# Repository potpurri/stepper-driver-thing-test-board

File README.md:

# stepper-driver-thing-test-board

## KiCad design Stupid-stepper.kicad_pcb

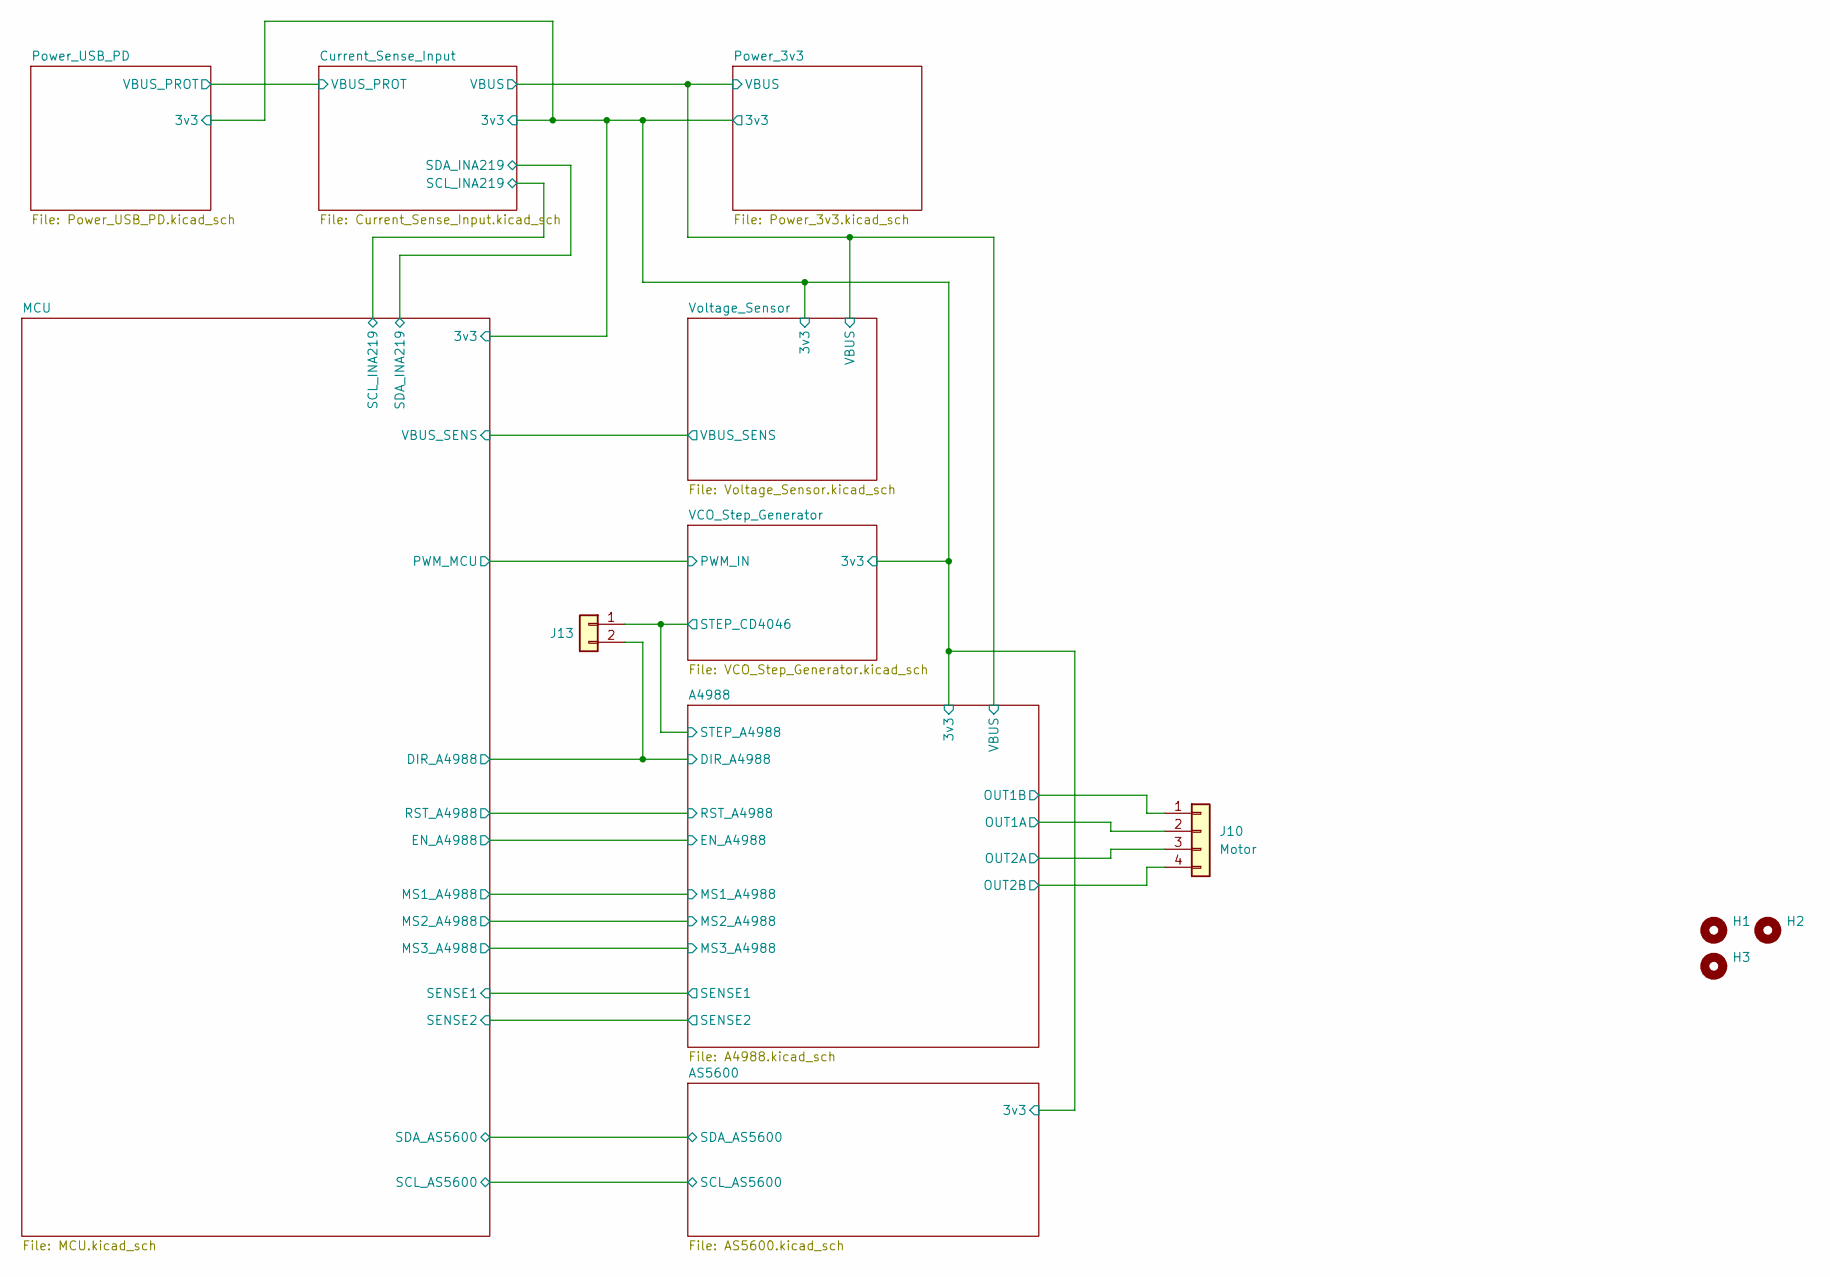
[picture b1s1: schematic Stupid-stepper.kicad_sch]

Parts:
H1, H2, H3: MountingHole; MountingHole_3.2mm_M3_DIN965_Pad_TopBottom
J10: Motor; JST_PH_B4B-PH-K_1x04_P2.00mm_Vertical
J13: Conn_01x02; PinHeader_1x02_P2.54mm_Vertical

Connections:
/A4988/DIR_A4988: J13.2; also elsewhere on the board
/A4988/OUT1A: J10.2; also elsewhere on the board
/A4988/OUT1B: J10.1; also elsewhere on the board
/A4988/OUT2A: J10.3; also elsewhere on the board
/A4988/OUT2B: J10.4; also elsewhere on the board
/A4988/STEP_A4988: J13.1; also elsewhere on the board

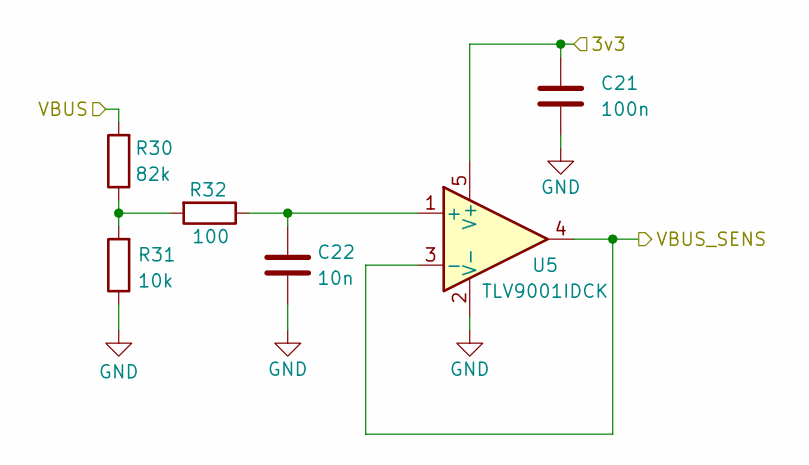
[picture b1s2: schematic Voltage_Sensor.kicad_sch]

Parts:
C21: 100n; C_0603_1608Metric
C22: 10n; C_0603_1608Metric
R30: 82k; R_0603_1608Metric
R31: 10k; R_0603_1608Metric
R32: 100; R_0603_1608Metric
U5: TLV9001IDCK; SOT-353_SC-70-5

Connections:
+3.3V: C21.1, U5.5 (V+); also elsewhere on the board
/MCU/VBUS_SENS: U5.3 (-), U5.4; also elsewhere on the board
GND: C21.2, C22.2, R31.1, U5.2 (V-); also elsewhere on the board
unnamed: R30.1, R31.2, R32.2
unnamed: C22.1, R32.1, U5.1 (+)
VBUS: R30.2; also elsewhere on the board

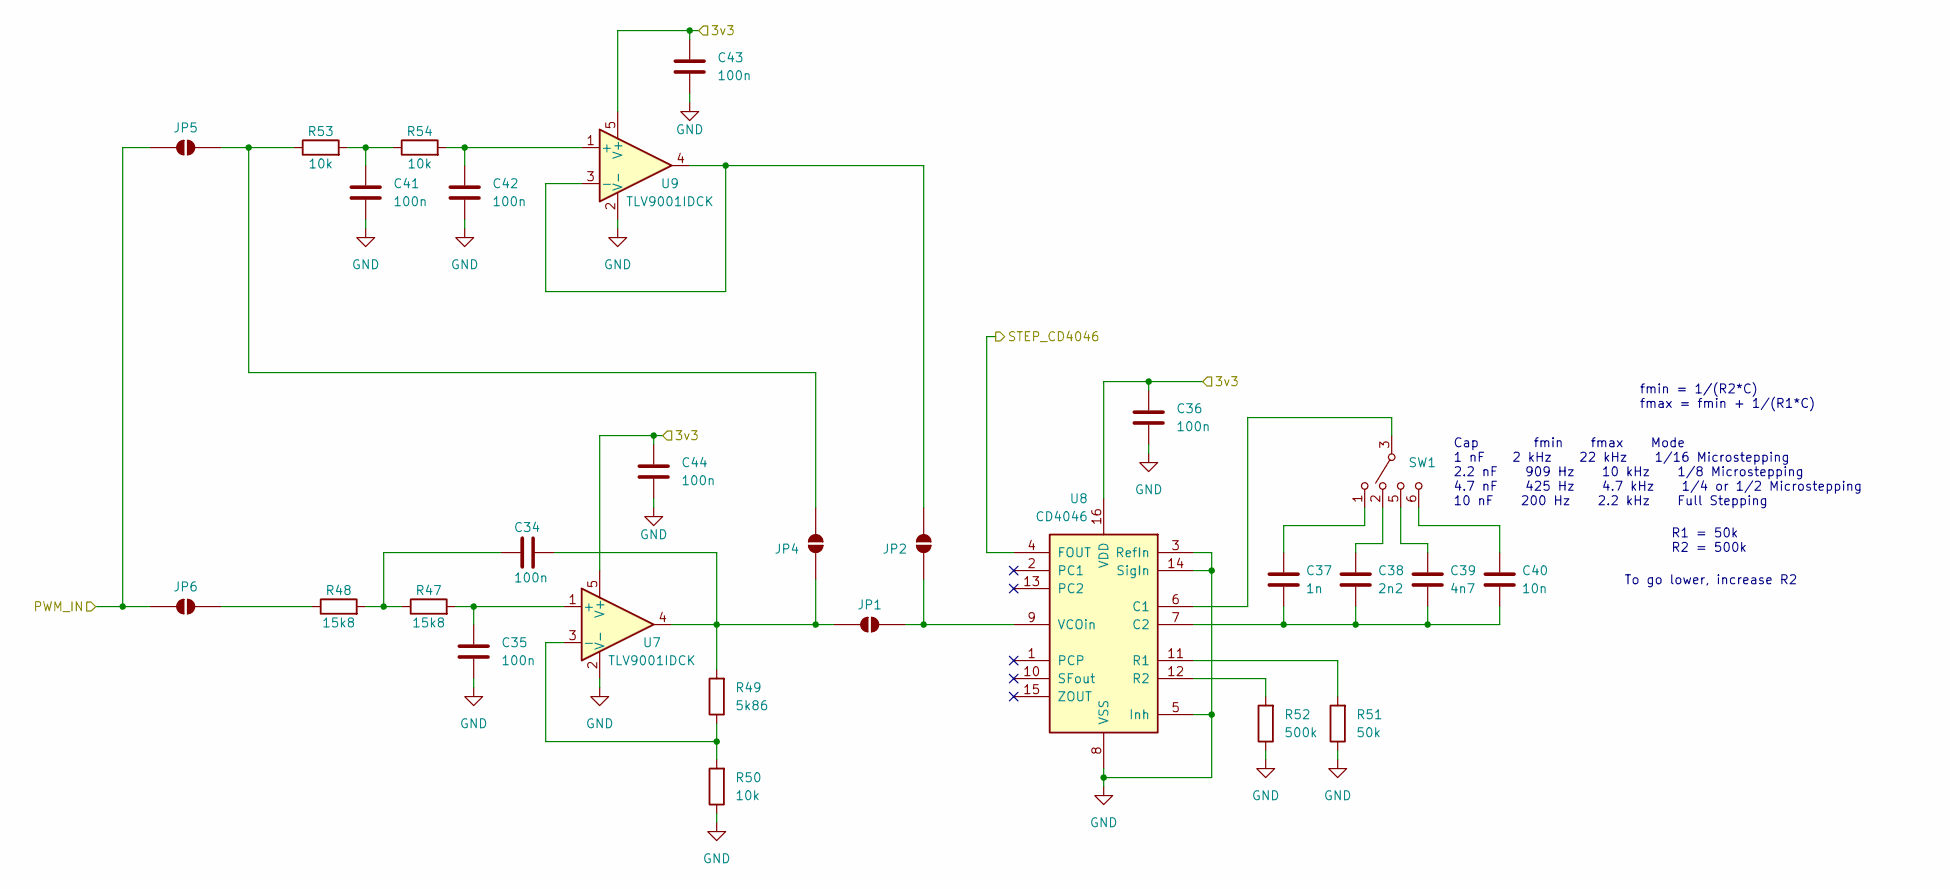
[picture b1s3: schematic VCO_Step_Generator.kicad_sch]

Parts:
C34, C35, C36, C41, C42, C43, C44: 100n; C_0603_1608Metric
C37: 1n; C_0603_1608Metric
C38: 2n2; C_0603_1608Metric
C39: 4n7; C_0603_1608Metric
C40: 10n; C_0603_1608Metric
JP1, JP2, JP4, JP5, JP6: SolderJumper_2_Open; SolderJumper-2_P1.3mm_Open_RoundedPad1.0x1.5mm
R47, R48: 15k8; R_0603_1608Metric
R49: 5k86; R_0603_1608Metric
R50, R53, R54: 10k; R_0603_1608Metric
R51: 50k; R_0603_1608Metric
R52: 500k; R_0603_1608Metric
SW1: mskt-14c01
U7, U9: TLV9001IDCK; SOT-353_SC-70-5
U8: CD4046; TSSOP-16_4.4x5mm_P0.65mm

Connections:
+3.3V: C36.1, C43.1, C44.1, U7.5 (V+), U8.16 (VDD), U9.5 (V+); also elsewhere on the board
/A4988/STEP_A4988: U8.4 (FOUT); also elsewhere on the board
/MCU/PWM_MCU: JP5.1 (A), JP6.1 (A); also elsewhere on the board
GND: C35.2, C36.2, C41.2, C42.2, C43.2, C44.2, R50.1, R51.1, R52.1, U7.2 (V-), U8.3 (RefIn), U8.5 (Inh), U8.8 (VSS), U8.14 (SigIn), U9.2 (V-); also elsewhere on the board
unnamed: C34.2, R47.1, R48.2
unnamed: C37.1, SW1.1
unnamed: C38.1, SW1.2
unnamed: C39.1, SW1.5
unnamed: C40.1, SW1.6
unnamed: C41.1, R53.2, R54.1
unnamed: C34.1, JP1.1 (A), JP4.2 (B), R49.2, U7.4
unnamed: JP1.2 (B), JP2.2 (B), U8.9 (VCOin)
unnamed: JP2.1 (A), U9.3 (-), U9.4
unnamed: JP4.1 (A), JP5.2 (B), R53.1
unnamed: JP6.2 (B), R48.1
unnamed: C35.1, R47.2, U7.1 (+)
unnamed: R49.1, R50.2, U7.3 (-)
unnamed: SW1.3, SW1.4, U8.6 (C1)
unnamed: C37.2, C38.2, C39.2, C40.2, U8.7 (C2)
unnamed: R51.2, U8.11 (R1)
unnamed: R52.2, U8.12 (R2)
unnamed: C42.1, R54.2, U9.1 (+)

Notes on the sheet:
R1 = 50k R2 = 500k
fmin = 1/(R2*C) fmax = fmin + 1/(R1*C)
To go lower, increase R2
Cap fmin fmax Mode 1 nF 2 kHz 22 kHz 1/16 Microstepping 2.2 nF 909 Hz 10 kHz 1/8 Microstepping 4.7 nF 425 Hz 4.7 kHz 1/4 or 1/2 Microstepping 10 nF 200 Hz 2.2 kHz Full Stepping

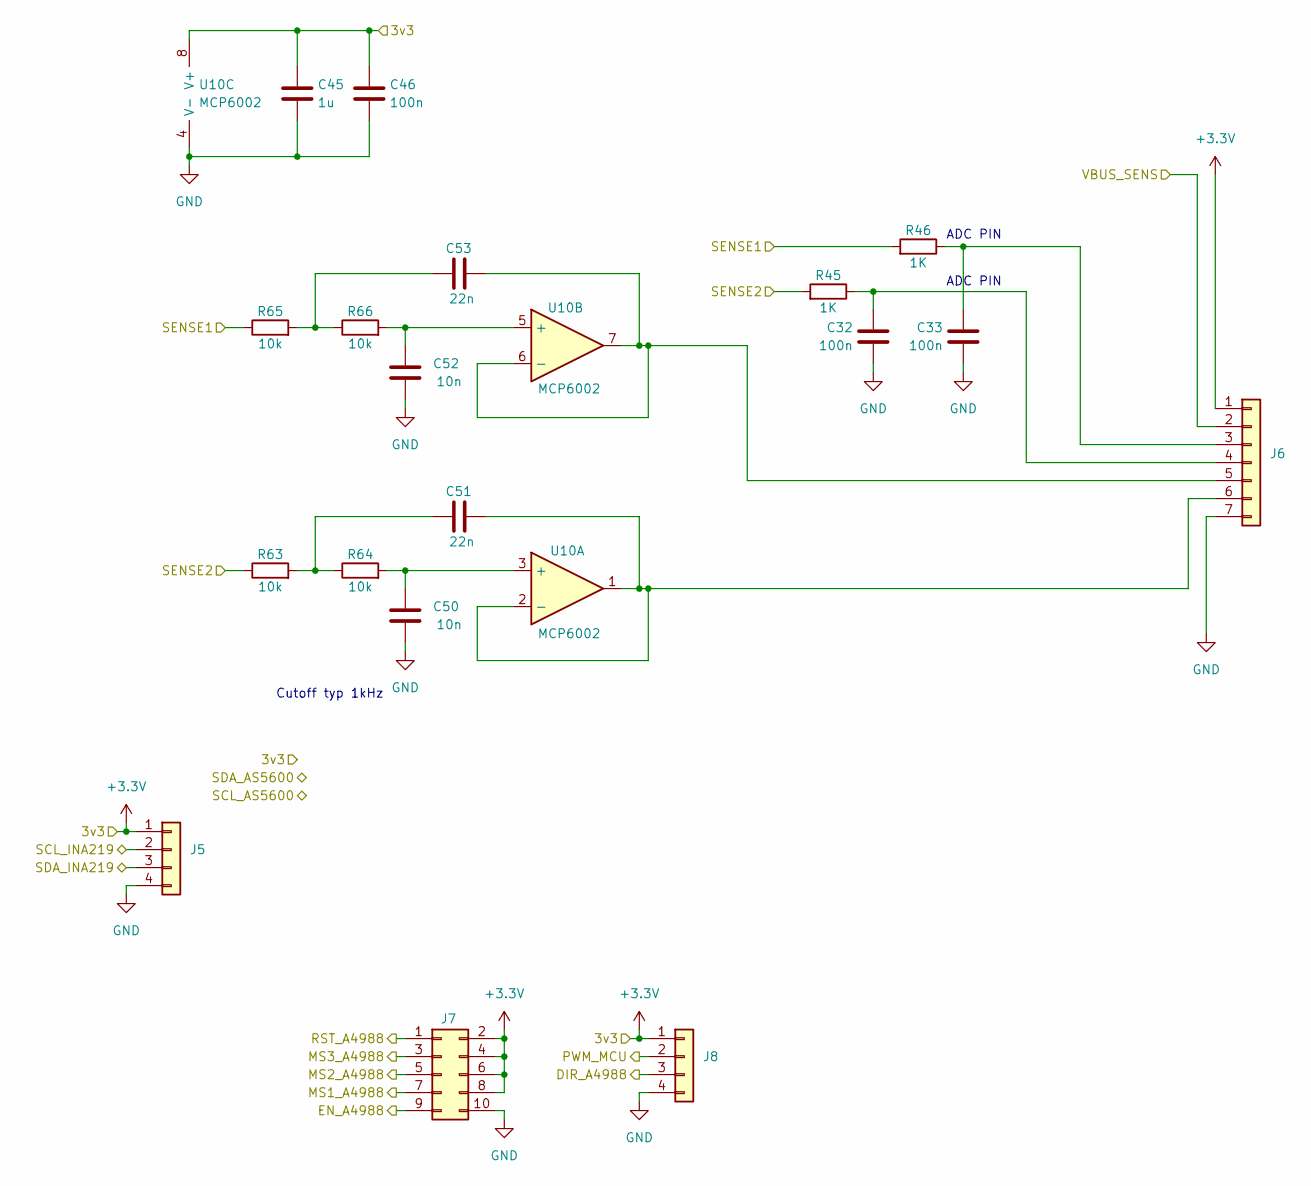
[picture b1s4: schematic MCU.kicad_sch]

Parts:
C32, C33, C46: 100n; C_0603_1608Metric
C45: 1u; C_0603_1608Metric
C50, C52: 10n; C_0603_1608Metric
C51, C53: 22n; C_0603_1608Metric
J5, J8: Conn_01x04; PinHeader_1x04_P2.54mm_Vertical
J6: Conn_01x07; PinHeader_1x07_P2.54mm_Vertical
J7: Conn_02x05_Odd_Even; PinHeader_2x05_P2.54mm_Vertical
R45, R46: 1K; R_0603_1608Metric
R63, R64, R65, R66: 10k; R_0603_1608Metric
U10: ﻿MCP6002; SOIC-8_3.9x4.9mm_P1.27mm

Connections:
+3.3V: C45.1, C46.1, J5.1, J6.1, J7.2, J7.4, J7.6, J7.8, J8.1, U10.8 (V+); also elsewhere on the board
/A4988/DIR_A4988: J8.3; also elsewhere on the board
/A4988/EN_A4988: J7.9; also elsewhere on the board
/A4988/MS1_A4988: J7.7; also elsewhere on the board
/A4988/MS2_A4988: J7.5; also elsewhere on the board
/A4988/MS3_A4988: J7.3; also elsewhere on the board
/A4988/RST_A4988: J7.1; also elsewhere on the board
/A4988/SENSE1: R46.2, R65.1; also elsewhere on the board
/A4988/SENSE2: R45.2, R63.1; also elsewhere on the board
/Current_Sense_Input/SCL_INA219: J5.2; also elsewhere on the board
/Current_Sense_Input/SDA_INA219: J5.3; also elsewhere on the board
/MCU/PWM_MCU: J8.2; also elsewhere on the board
/MCU/VBUS_SENS: J6.2; also elsewhere on the board
GND: C32.2, C33.2, C45.2, C46.2, C50.2, C52.2, J5.4, J6.7, J7.10, J8.4, U10.4 (V-); also elsewhere on the board
unnamed: C51.2, R63.2, R64.1
unnamed: C53.2, R65.2, R66.1
unnamed: C33.1, J6.3, R46.1
unnamed: C32.1, J6.4, R45.1
unnamed: C53.1, J6.5, U10.6 (-), U10.7
unnamed: C51.1, J6.6, U10.1, U10.2 (-)
unnamed: C50.1, R64.2, U10.3 (+)
unnamed: C52.1, R66.2, U10.5 (+)

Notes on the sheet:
ADC PIN
Cutoff typ 1kHz

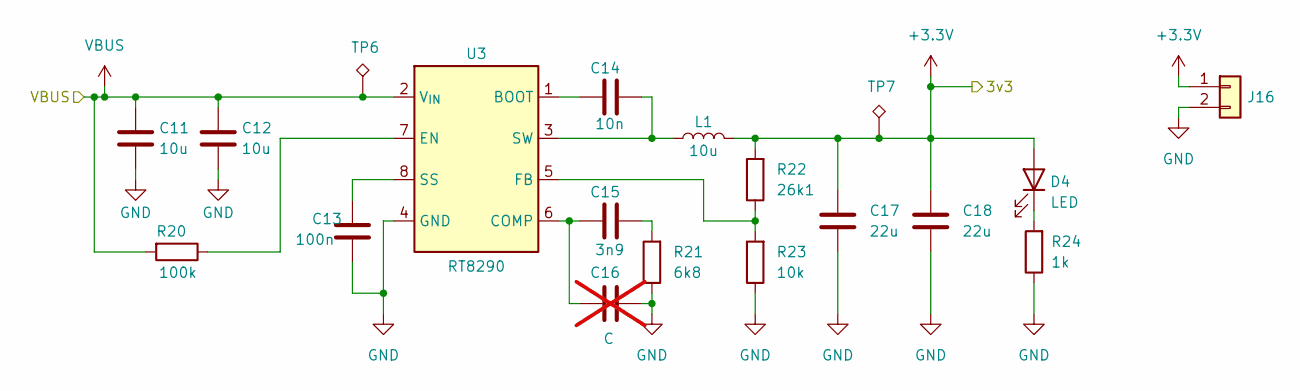
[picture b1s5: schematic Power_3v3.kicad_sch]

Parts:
C11, C12: 10u; C_1206_3216Metric
C13: 100n; C_0603_1608Metric
C14: 10n; C_0603_1608Metric
C15: 3n9; C_0603_1608Metric
C16: C; C_0603_1608Metric; not fitted
C17, C18: 22u; C_1206_3216Metric
D4: LED; LED_0805_2012Metric
J16: Conn_01x02; PinHeader_1x02_P2.54mm_Vertical
L1: 10u; L_APV_ANR5020
R20: 100k; R_0603_1608Metric
R21: 6k8; R_0603_1608Metric
R22: 26k1; R_0603_1608Metric
R23: 10k; R_0603_1608Metric
R24: 1k; R_0603_1608Metric
TP6, TP7: TestPoint_Alt; TestPoint_Pad_D1.0mm
U3: RT8290; Texas_HSOP-8-1EP_3.9x4.9mm_P1.27mm

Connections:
+3.3V: C17.1, C18.1, D4.2 (A), J16.1, L1.2, R22.2, TP7.1 (1_1); also elsewhere on the board
GND: C11.2, C12.2, C13.2, C16.2, C17.2, C18.2, J16.2, R21.1, R23.1, R24.1, U3.4 (GND), U3.9 (GND); also elsewhere on the board
unnamed: C15.2, R21.2
unnamed: D4.1 (K), R24.2
unnamed: C14.1, U3.1 (BOOT)
unnamed: C15.1, C16.1, U3.6 (COMP)
unnamed: R20.1, U3.7 (EN)
unnamed: R22.1, R23.2, U3.5 (FB)
unnamed: C13.1, U3.8 (SS)
unnamed: C14.2, L1.1, U3.3 (SW)
VBUS: C11.1, C12.1, R20.2, TP6.1 (1_1), U3.2 (V_{IN}); also elsewhere on the board

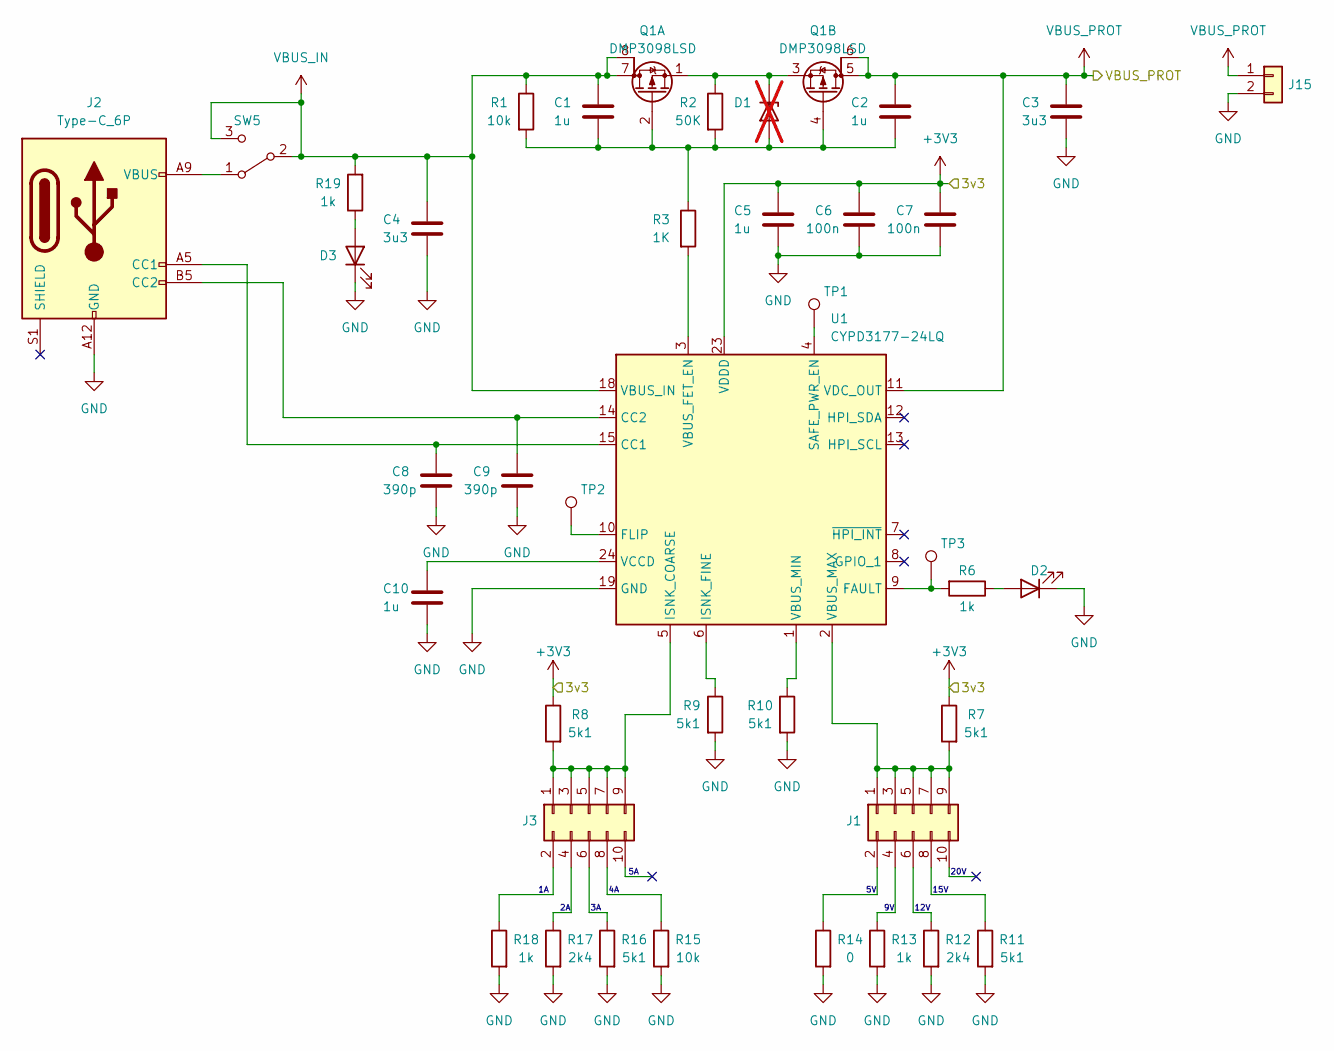
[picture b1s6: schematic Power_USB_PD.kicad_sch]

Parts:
C1, C2, C5, C10: 1u; C_0805_2012Metric_Pad1.18x1.45mm_HandSolder
C3, C4: 3u3; C_0805_2012Metric_Pad1.18x1.45mm_HandSolder
C6, C7: 100n; C_0603_1608Metric_Pad1.08x0.95mm_HandSolder
C8, C9: 390p; C_0603_1608Metric_Pad1.08x0.95mm_HandSolder
D1: D_Zener; D_DO-35_SOD27_P7.62mm_Horizontal; not fitted
D2, D3: LED; LED_0805_2012Metric
J1, J3: Conn_02x05_Odd_Even; PinHeader_2x05_P2.54mm_Vertical
J2: Type-C_6P; USB_C_Receptacle_HRO_TYPE-C-31-M-17
J15: Conn_01x02; PinHeader_1x02_P2.54mm_Vertical
Q1: DMP3098LSD; SOIC-8-1EP_3.9x4.9mm_P1.27mm_EP2.29x3mm
R1, R15: 10k; R_0603_1608Metric
R2: 50K; R_0603_1608Metric
R3: 1K; R_0603_1608Metric
R6, R13, R18, R19: 1k; R_0603_1608Metric
R7, R8, R9, R10, R11, R16: 5k1; R_0603_1608Metric
R12, R17: 2k4; R_0603_1608Metric
R14: 0; R_0603_1608Metric
SW5: SW_SPDT; Schiebeschalter SS-12D00
TP1, TP2, TP3: TestPoint; TestPoint_Pad_1.0x1.0mm
U1: CYPD3177-24LQ; QFN-24-1EP_4x4mm_P0.5mm_EP2.75x2.75mm_ThermalVias

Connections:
+3.3V: C5.1, C6.1, C7.1, R7.1, R8.1, U1.23 (VDDD); also elsewhere on the board
GND: C3.2, C4.2, C5.2, C6.2, C7.2, C8.2, C9.2, C10.2, D2.1 (K), D3.1 (K), J2.A12 (GND), J2.B12 (GND), J15.2, R9.2, R10.2, R11.2, R12.2, R13.2, R14.2, R15.2, R16.2, R17.2, R18.2, U1.19 (GND), U1.22 (GND), U1.25 (GND); also elsewhere on the board
unnamed: C1.2, C2.2, D1.2 (A), Q1.2 (G), Q1.4 (G), R1.2, R2.2, R3.1
unnamed: D1.1 (K), Q1.1 (S), Q1.3 (S), R2.1
unnamed: D2.2 (A), R6.1
unnamed: D3.2 (A), R19.1
unnamed: J1.1, J1.3, J1.5, J1.7, J1.9, R7.2, U1.2 (VBUS_MAX)
unnamed: J1.2, R14.1
unnamed: J1.4, R13.1
unnamed: J1.6, R12.1
unnamed: J1.8, R11.1
unnamed: C8.1, J2.A5 (CC1), U1.15 (CC1)
unnamed: C9.1, J2.B5 (CC2), U1.14 (CC2)
unnamed: J3.1, J3.3, J3.5, J3.7, J3.9, R8.2, U1.5 (ISNK_COARSE)
unnamed: J3.2, R18.1
unnamed: J3.4, R17.1
unnamed: J3.6, R16.1
unnamed: J3.8, R15.1
unnamed: J2.A9 (VBUS), J2.B9 (VBUS), SW5.1 (A)
unnamed: R6.2, TP3.1 (1_1), U1.9 (FAULT)
unnamed: TP2.1 (1_1), U1.10 (FLIP)
unnamed: R9.1, U1.6 (ISNK_FINE)
unnamed: TP1.1 (1_1), U1.4 (SAFE_PWR_EN)
unnamed: R3.2, U1.3 (VBUS_FET_EN)
unnamed: R10.1, U1.1 (VBUS_MIN)
unnamed: C10.1, U1.24 (VCCD)
VBUS_IN: C1.1, C4.1, Q1.7 (D), Q1.8 (G), R1.1, R19.2, SW5.2 (B), SW5.3 (C), U1.18 (VBUS_IN)
VBUS_PROT: C2.1, C3.1, J15.1, Q1.5 (D), Q1.6 (G), U1.11 (VDC_OUT); also elsewhere on the board

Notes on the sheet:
15V
20V
12V

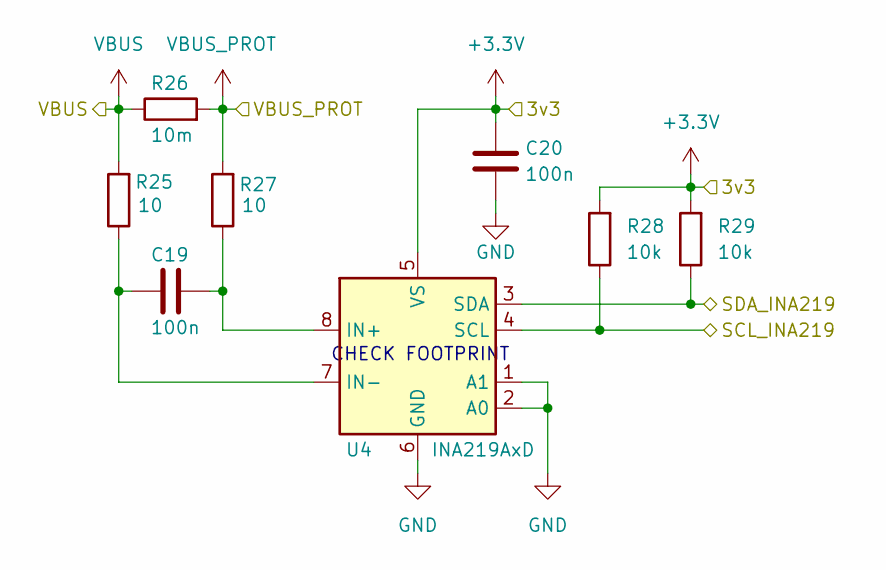
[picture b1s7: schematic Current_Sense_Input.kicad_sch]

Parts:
C19, C20: 100n; C_0603_1608Metric
R25, R27: 10; R_0603_1608Metric
R26: 10m; R_2512_6332Metric
R28, R29: 10k; R_0603_1608Metric
U4: INA219AxD; SOIC-8_3.9x4.9mm_P1.27mm

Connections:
+3.3V: C20.1, R28.2, R29.2, U4.5 (VS); also elsewhere on the board
/Current_Sense_Input/SCL_INA219: R28.1, U4.4 (SCL); also elsewhere on the board
/Current_Sense_Input/SDA_INA219: R29.1, U4.3 (SDA); also elsewhere on the board
GND: C20.2, U4.1 (A1), U4.2 (A0), U4.6 (GND); also elsewhere on the board
unnamed: C19.1, R27.1, U4.8 (IN+)
unnamed: C19.2, R25.1, U4.7 (IN-)
VBUS: R25.2, R26.1; also elsewhere on the board
VBUS_PROT: R26.2, R27.2; also elsewhere on the board

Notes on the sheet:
CHECK FOOTPRINT

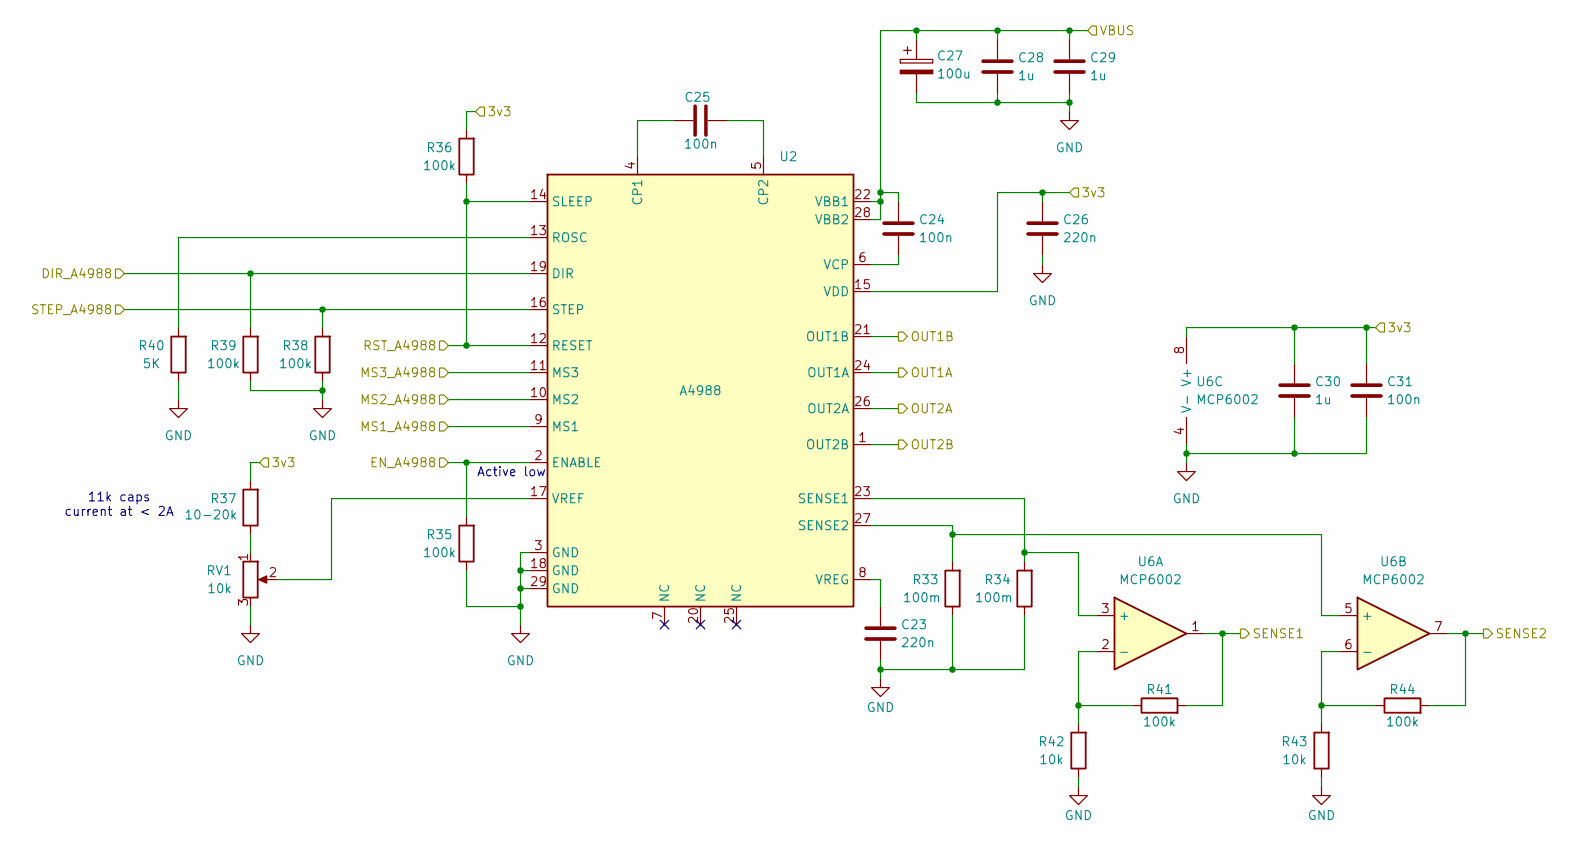
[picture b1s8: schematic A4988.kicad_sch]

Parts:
C23, C26: 220n; C_0603_1608Metric
C24, C25, C31: 100n; C_0603_1608Metric
C27: 100u; CP_Elec_8x10.5
C28, C29, C30: 1u; C_0603_1608Metric
R33, R34: 100m; R_1206_3216Metric
R35, R36, R38, R39, R41, R44: 100k; R_0603_1608Metric
R37: 10-20k; R_0603_1608Metric
R40: 5K; R_0603_1608Metric
R42, R43: 10k; R_0603_1608Metric
RV1: 10k; Potentiometer_Bourns_TC33X_Vertical
U2: A4988; VQFN-28-1EP_5x5mm_P0.5mm_EP3.25x3.25mm_ThermalVias
U6: ﻿MCP6002; SOIC-8_3.9x4.9mm_P1.27mm

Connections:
+3.3V: C26.1, C30.1, C31.1, R36.2, R37.2, U2.15 (VDD), U6.8 (V+); also elsewhere on the board
/A4988/DIR_A4988: R39.2, U2.19 (DIR); also elsewhere on the board
/A4988/EN_A4988: R35.2, U2.2 (ENABLE); also elsewhere on the board
/A4988/MS1_A4988: U2.9 (MS1); also elsewhere on the board
/A4988/MS2_A4988: U2.10 (MS2); also elsewhere on the board
/A4988/MS3_A4988: U2.11 (MS3); also elsewhere on the board
/A4988/OUT1A: U2.24 (OUT1A); also elsewhere on the board
/A4988/OUT1B: U2.21 (OUT1B); also elsewhere on the board
/A4988/OUT2A: U2.26 (OUT2A); also elsewhere on the board
/A4988/OUT2B: U2.1 (OUT2B); also elsewhere on the board
/A4988/RST_A4988: R36.1, U2.12 (RESET), U2.14 (SLEEP); also elsewhere on the board
/A4988/SENSE1: R41.2, U6.1; also elsewhere on the board
/A4988/SENSE2: R44.2, U6.7; also elsewhere on the board
/A4988/STEP_A4988: R38.2, U2.16 (STEP); also elsewhere on the board
GND: C23.2, C26.2, C27.2, C28.2, C29.2, C30.2, C31.2, R33.1, R34.1, R35.1, R38.1, R39.1, R40.1, R42.1, R43.1, RV1.3, U2.3 (GND), U2.18 (GND), U2.29 (GND), U6.4 (V-); also elsewhere on the board
unnamed: R37.1, RV1.1
unnamed: C25.1, U2.4 (CP1)
unnamed: C25.2, U2.5 (CP2)
unnamed: R40.2, U2.13 (ROSC)
unnamed: R34.2, U2.23 (SENSE1), U6.3 (+)
unnamed: R33.2, U2.27 (SENSE2), U6.5 (+)
unnamed: C24.2, U2.6 (VCP)
unnamed: RV1.2, U2.17 (VREF)
unnamed: C23.1, U2.8 (VREG)
unnamed: R41.1, R42.2, U6.2 (-)
unnamed: R43.2, R44.1, U6.6 (-)
VBUS: C24.1, C27.1, C28.1, C29.1, U2.22 (VBB1), U2.28 (VBB2); also elsewhere on the board

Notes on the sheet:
Active low
11k caps current at < 2A

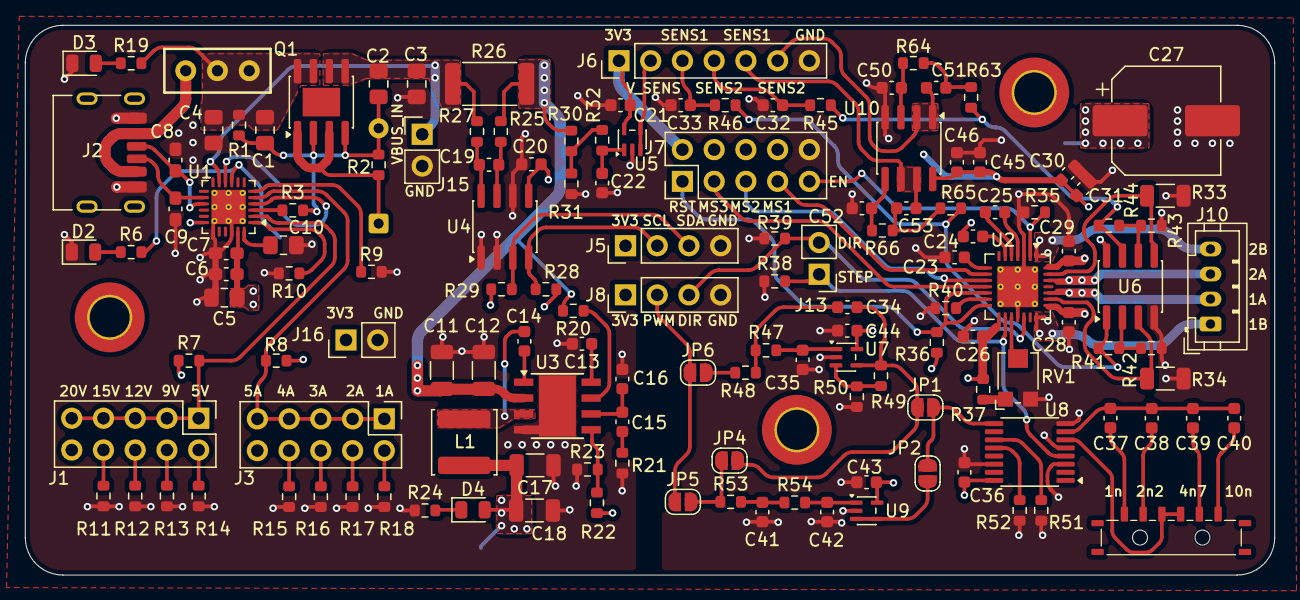
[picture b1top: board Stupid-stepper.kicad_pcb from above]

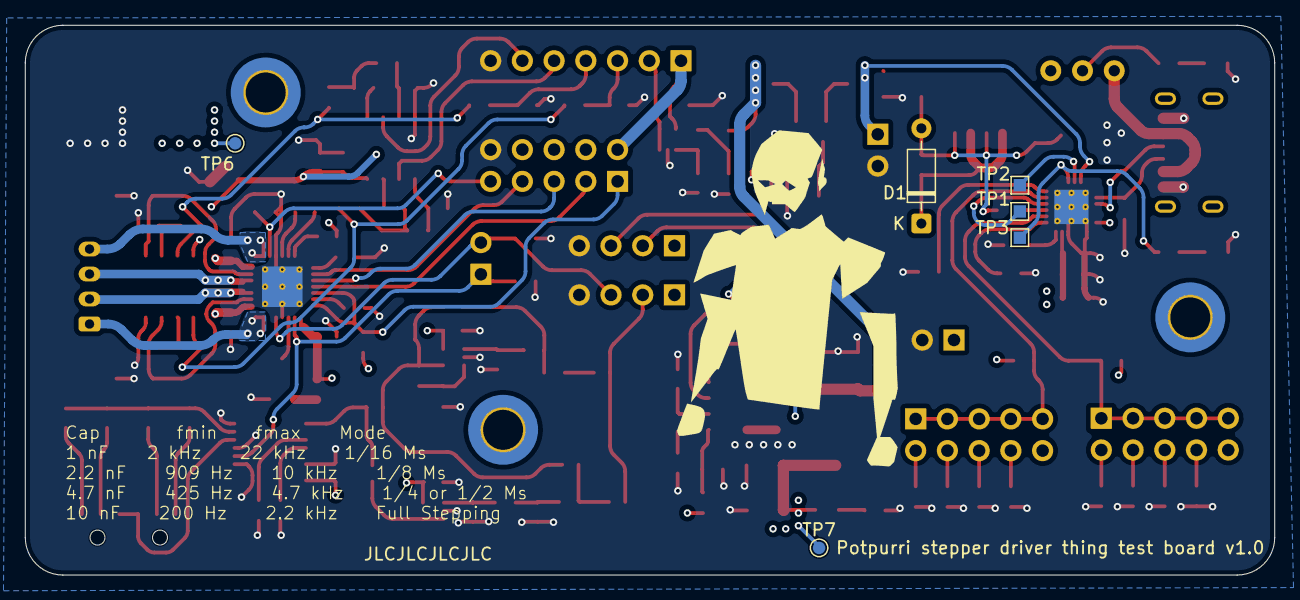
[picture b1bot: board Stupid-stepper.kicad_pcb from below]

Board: 4 copper layers, 100.0 x 44.0 mm, 149 parts (6 on the bottom side), 95 nets.
